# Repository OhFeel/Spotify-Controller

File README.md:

# Spotify Controller Hackpad

A custom macropad for Spotify control, built with a Seeed XIAO (RP2040), rotary encoder, RGB lighting, and OLED support.

## Screenshot: Overall Hackpad

## Screenshot: Schematic

## Screenshot: PCB

## Screenshot: Case + Fit Together

## BOM (Bill of Materials)

|  Id | Designator                                                       | Footprint                                      | Quantity | Designation           | Supplier Link                                                                                                   |
| --: | ---------------------------------------------------------------- | ---------------------------------------------- | -------: | --------------------- | --------------------------------------------------------------------------------------------------------------- |
|   1 | D18, D16, D17, D22, D19, D20, D21                                | D_DO-35_SOD27_P7.62mm_Horizontal               |        7 | 1N4148                | [LCSC - 1N4148](https://www.lcsc.com/search?q=1N4148)                                                           |
|   2 | D1, D7, D2, D8, D3, D9, D4, D10, D6, D5, D12, D11, D15, D14, D13 | SK6812MINI-E_fixed                             |       15 | SK6812MINI-E          | [LCSC - SK6812MINI-E](https://www.lcsc.com/search?q=SK6812MINI-E)                                               |
|   3 | U1                                                               | XIAO-Generic-Hybrid-14P-2.54-21X17.8MM         |        1 | MOUDLE-SEEEDUINO-XIAO | [Seeed Studio - XIAO RP2040](https://www.seeedstudio.com/XIAO-RP2040-v1-0-p-5026.html)                          |
|   4 | SW1                                                              | RotaryEncoder_Alps_EC11E-Switch_Vertical_H20mm |        1 | RotaryEncoder_Switch  | [Mouser - EC11 encoders](https://www.mouser.com/c/electromechanical/encoders/?q=EC11)                           |
|   5 | SW3, SW5, SW7, SW4, SW6, SW2                                     | SW_Cherry_MX_1.00u_Plate                       |        6 | SW_Push               | [AliExpress - Cherry MX switches](https://www.aliexpress.com/wholesale?SearchText=cherry+mx+switch)             |
|   6 | J1                                                               | SSD1306-0.91-OLED-4pin-128x32                  |        1 | Conn_01x04_Pin        | [AliExpress - 0.91" SSD1306 OLED](https://www.aliexpress.com/wholesale?SearchText=0.91+inch+ssd1306+oled+4+pin) |
|   7 | N/A                                                              | N/A                                            |        6 | DSA Keycap            | [AliExpress - DSA keycaps](https://www.aliexpress.com/wholesale?SearchText=DSA+keycap)                          |
|   8 | N/A                                                              | N/A                                            |        6 | M3 Screw              | [AliExpress - M3 screws](https://www.aliexpress.com/wholesale?SearchText=M3+screw)                              |

## Firmware Notes

- QMK-based firmware files live in [Firmware/](Firmware/).
- Main keymap: [Firmware/keymap.c](Firmware/keymap.c)
- Hardware config: [Firmware/config.h](Firmware/config.h)
- Keyboard metadata: [Firmware/info.json](Firmware/info.json)

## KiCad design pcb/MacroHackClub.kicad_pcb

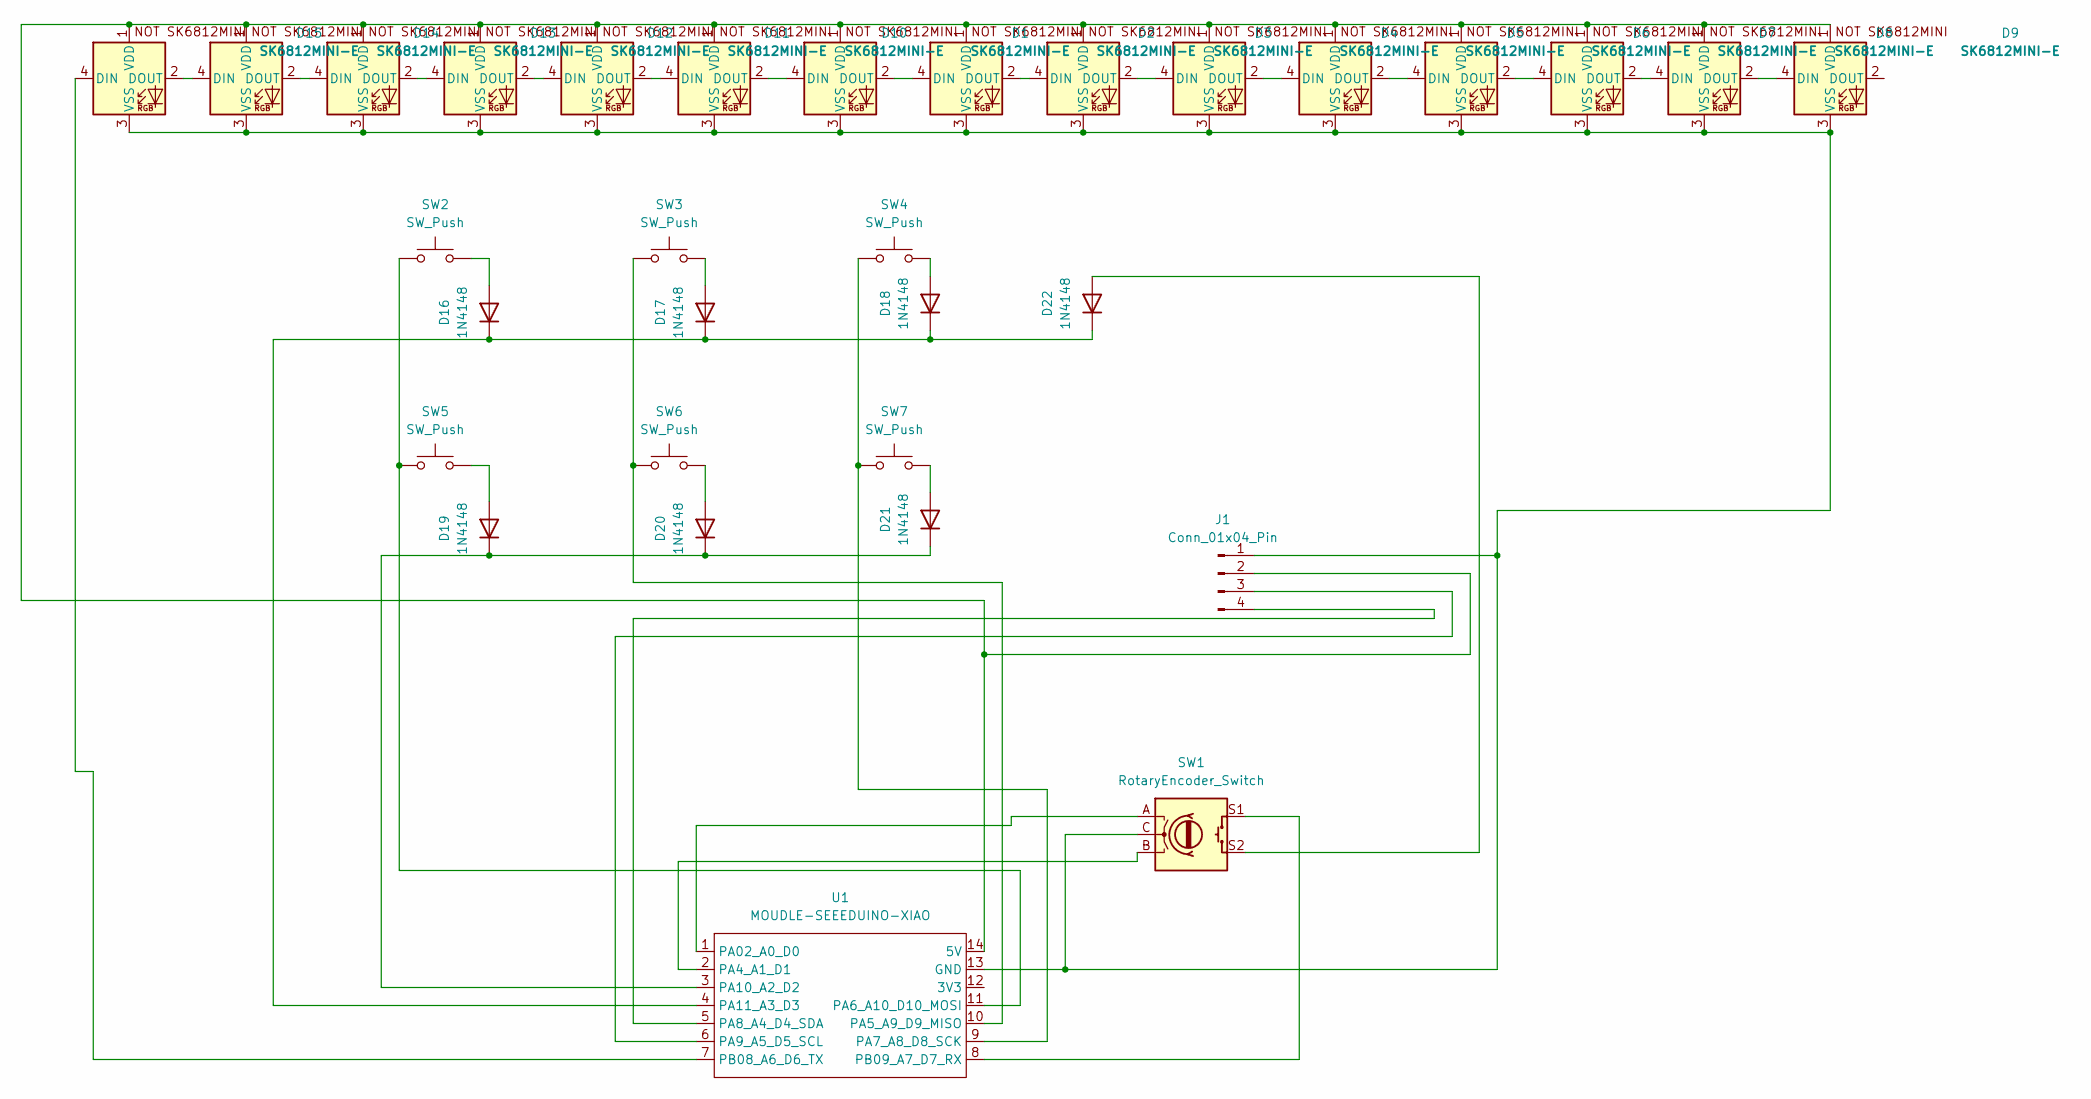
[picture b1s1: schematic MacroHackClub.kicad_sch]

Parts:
D1, D2, D3, D4, D5, D6, D7, D8, D9, D10, D11, D12, D13, D14, D15: SK6812MINI-E; SK6812MINI-E_fixed
D16, D17, D18, D19, D20, D21, D22: 1N4148; D_DO-35_SOD27_P7.62mm_Horizontal
J1: Conn_01x04_Pin; SSD1306-0.91-OLED-4pin-128x32
SW1: RotaryEncoder_Switch; RotaryEncoder_Alps_EC11E-Switch_Vertical_H20mm
SW2, SW3, SW4, SW5, SW6, SW7: SW_Push; SW_Cherry_MX_1.00u_Plate
U1: MOUDLE-SEEEDUINO-XIAO; XIAO-Generic-Hybrid-14P-2.54-21X17.8MM

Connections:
unnamed: D1.4 (DIN), D10.2 (DOUT)
unnamed: D1.2 (DOUT), D2.4 (DIN)
unnamed: D1.1 (VDD), D2.1 (VDD), D3.1 (VDD), D4.1 (VDD), D5.1 (VDD), D6.1 (VDD), D7.1 (VDD), D8.1 (VDD), D9.1 (VDD), D10.1 (VDD), D11.1 (VDD), D12.1 (VDD), D13.1 (VDD), D14.1 (VDD), D15.1 (VDD), J1.2, U1.14 (5V)
unnamed: D1.3 (VSS), D2.3 (VSS), D3.3 (VSS), D4.3 (VSS), D5.3 (VSS), D6.3 (VSS), D7.3 (VSS), D8.3 (VSS), D9.3 (VSS), D10.3 (VSS), D11.3 (VSS), D12.3 (VSS), D13.3 (VSS), D14.3 (VSS), D15.3 (VSS), J1.1, SW1.C, U1.13 (GND)
unnamed: D2.2 (DOUT), D3.4 (DIN)
unnamed: D3.2 (DOUT), D4.4 (DIN)
unnamed: D4.2 (DOUT), D5.4 (DIN)
unnamed: D5.2 (DOUT), D6.4 (DIN)
unnamed: D6.2 (DOUT), D7.4 (DIN)
unnamed: D7.2 (DOUT), D8.4 (DIN)
unnamed: D8.2 (DOUT), D9.4 (DIN)
unnamed: D10.4 (DIN), D11.2 (DOUT)
unnamed: D11.4 (DIN), D12.2 (DOUT)
unnamed: D12.4 (DIN), D13.2 (DOUT)
unnamed: D13.4 (DIN), D14.2 (DOUT)
unnamed: D14.4 (DIN), D15.2 (DOUT)
unnamed: D15.4 (DIN), U1.7 (PB08_A6_D6_TX)
unnamed: D16.2 (A), SW2.2
unnamed: D16.1 (K), D17.1 (K), D18.1 (K), D22.1 (K), U1.4 (PA11_A3_D3)
unnamed: D17.2 (A), SW3.2
unnamed: D18.2 (A), SW4.2
unnamed: D19.2 (A), SW5.2
unnamed: D19.1 (K), D20.1 (K), D21.1 (K), U1.3 (PA10_A2_D2)
unnamed: D20.2 (A), SW6.2
unnamed: D21.2 (A), SW7.2
unnamed: D22.2 (A), SW1.S2
unnamed: J1.3, U1.6 (PA9_A5_D5_SCL)
unnamed: J1.4, U1.5 (PA8_A4_D4_SDA)
unnamed: SW1.A, U1.1 (PA02_A0_D0)
unnamed: SW1.B, U1.2 (PA4_A1_D1)
unnamed: SW3.1, SW6.1, U1.10 (PA5_A9_D9_MISO)
unnamed: SW2.1, SW5.1, U1.11 (PA6_A10_D10_MOSI)
unnamed: SW4.1, SW7.1, U1.9 (PA7_A8_D8_SCK)
unnamed: SW1.S1, U1.8 (PB09_A7_D7_RX)

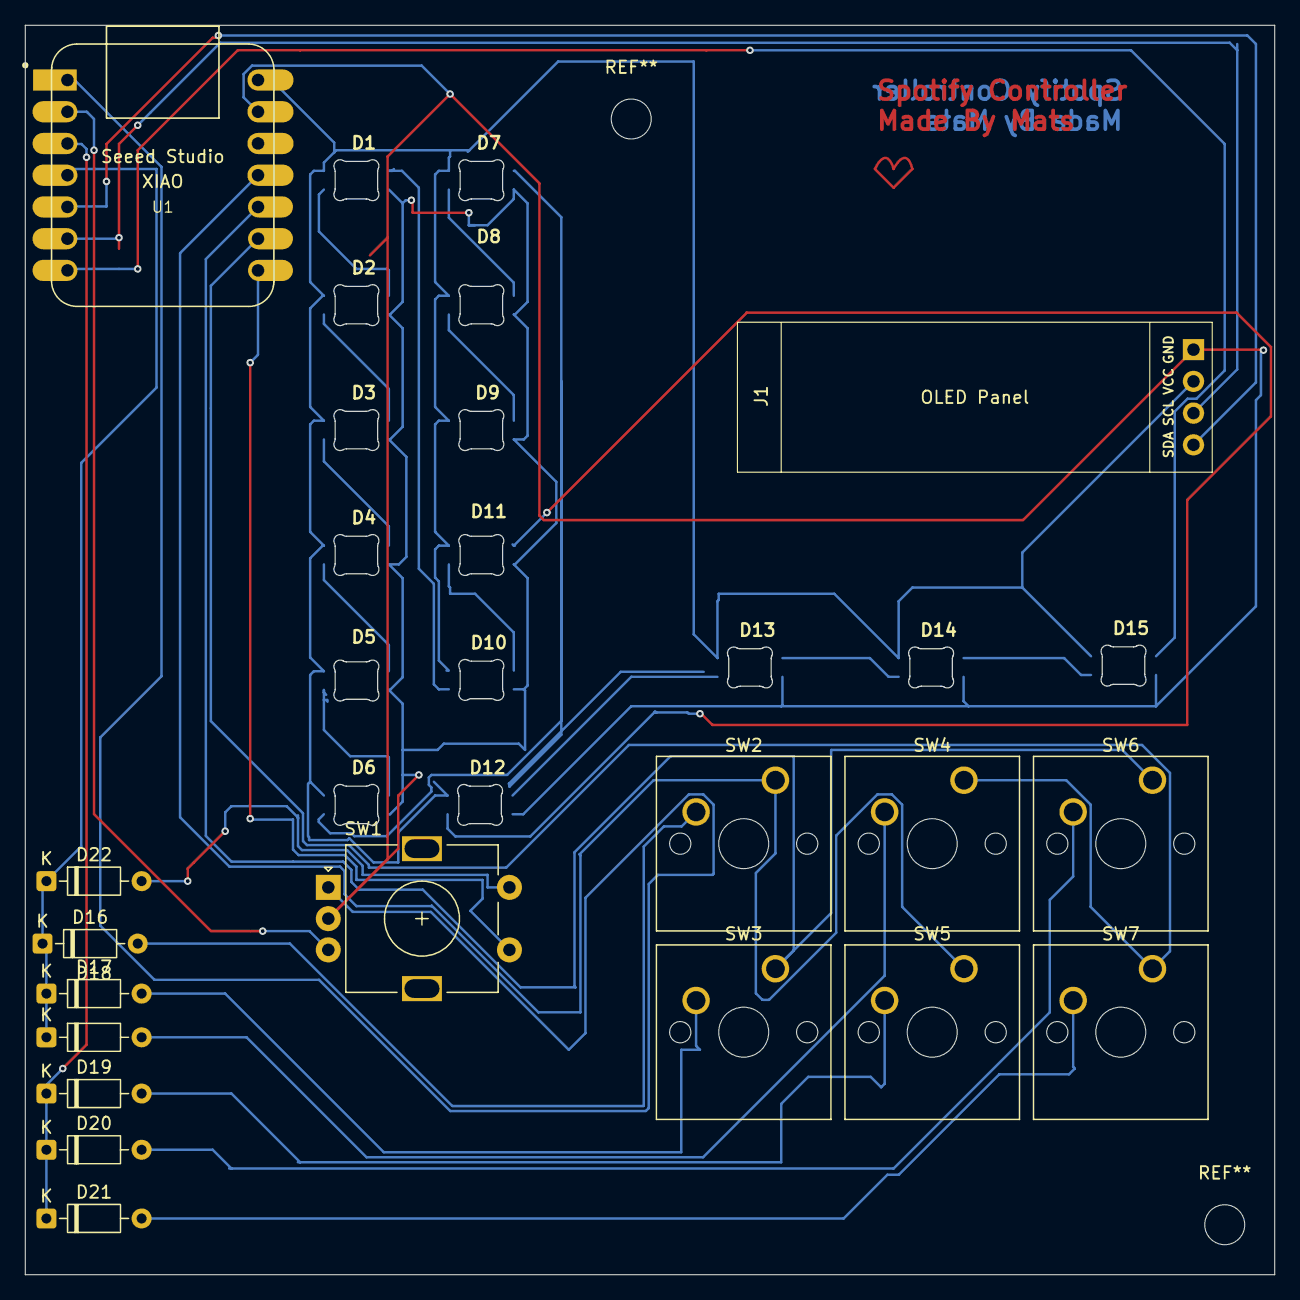
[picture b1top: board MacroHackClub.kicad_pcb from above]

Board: 2 copper layers, 99.9 x 100.0 mm, 31 parts (0 on the bottom side), 34 nets.

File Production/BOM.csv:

"Id";"Designator";"Footprint";"Quantity";"Designation";"Supplier and ref";
1;"D18,D16,D17,D22,D19,D20,D21";"D_DO-35_SOD27_P7.62mm_Horizontal";7;"1N4148";;;
2;"D1,D7,D2,D8,D3,D9,D4,D10,D6,D5,D12,D11,D15,D14,D13";"SK6812MINI-E_fixed";15;"SK6812MINI-E";;;
3;"U1";"XIAO-Generic-Hybrid-14P-2.54-21X17.8MM";1;"MOUDLE-SEEEDUINO-XIAO";;;
4;"SW1";"RotaryEncoder_Alps_EC11E-Switch_Vertical_H20mm";1;"RotaryEncoder_Switch";;;
5;"SW3,SW5,SW7,SW4,SW6,SW2";"SW_Cherry_MX_1.00u_Plate";6;"SW_Push";;;
6;"J1";"SSD1306-0.91-OLED-4pin-128x32";1;"Conn_01x04_Pin";;;

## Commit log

2026-03-01 Refactor code structure for improved readability and maintainability
2026-03-02 New case
2026-03-04 added schematic
2026-03-05 fixed issue
2026-03-05 Update BOM with supplier links and improve formatting in README
2026-03-06 updated BOM
